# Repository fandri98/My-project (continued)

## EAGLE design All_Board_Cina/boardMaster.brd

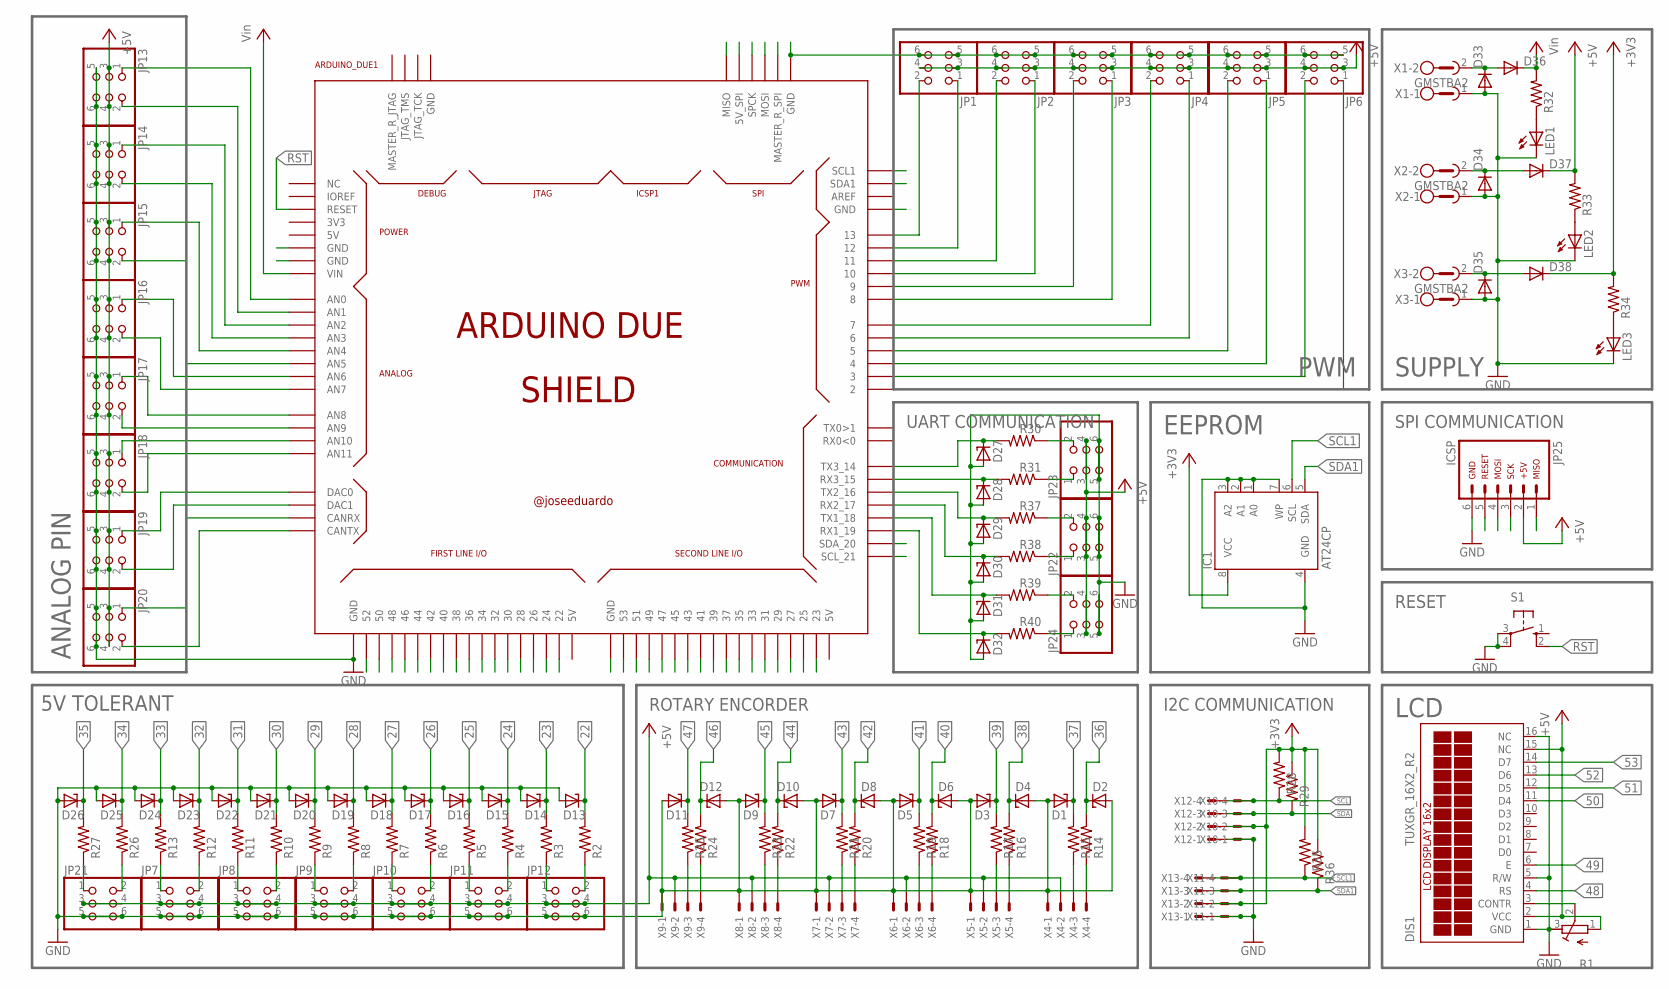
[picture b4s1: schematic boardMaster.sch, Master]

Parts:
ARDUINO_DUE1: ARDUINO_DUE_SHIELD
D1, D2, D3, D4, D5, D6, D7, D8, D9, D10, D11, D12, D13, D14, D15, D16, D17, D18, D19, D20, D21, D22, D23, D24, D25, D26, D27, D28, D29, D30, D31, D32: ZENER-DIODESOD80C; SOD80C
D33, D34, D35, D36, D37, D38: DIODE-DO214AA; DO214AA
DIS1: TUXGR_16X2_R2
IC1: AT24CP; DIL08
JP1, JP2, JP3, JP4, JP5, JP6, JP7, JP8, JP9, JP10, JP11, JP12, JP13, JP14, JP15, JP16, JP17, JP18, JP19, JP20, JP21, JP22, JP23, JP24: PINHD-2X3; 2X03
JP25: ARDUINO_CONN-ICSP; CONN-2X03
LED1, LED2, LED3: LEDCHIPLED_1206; CHIPLED_1206
R1: R-TRIMM64W; RTRIM64W
R2, R3, R4, R5, R6, R7, R8, R9, R10, R11, R12, R13, R14, R15, R16, R17, R18, R19, R20, R21, R22, R23, R24, R25, R26, R27, R28, R29, R30, R31, R32, R33, R34, R35, R36, R37, R38, R39, R40: R-US_R0805; R0805
S1: 40-XX; B3F-40XX
X1, X2, X3: GMSTBA2
X4, X5, X6, X7, X8, X9, X10, X11, X12, X13: 22-23-2041

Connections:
22: ARDUINO_DUE1.22, D13.C, R2.2
23: ARDUINO_DUE1.23, D14.C, R3.2
24: ARDUINO_DUE1.24, D15.C, R4.2
25: ARDUINO_DUE1.25, D16.C, R5.2
26: ARDUINO_DUE1.26, D17.C, R6.2
27: ARDUINO_DUE1.27, D18.C, R7.2
28: ARDUINO_DUE1.28, D19.C, R8.2
29: ARDUINO_DUE1.29, D20.C, R9.2
30: ARDUINO_DUE1.30, D21.C, R10.2
31: ARDUINO_DUE1.31, D22.C, R11.2
32: ARDUINO_DUE1.32, D23.C, R12.2
33: ARDUINO_DUE1.33, D24.C, R13.2
34: ARDUINO_DUE1.34, D25.C, R26.2
35: ARDUINO_DUE1.35, D26.C, R27.2
36: ARDUINO_DUE1.36, D2.C, R14.2
37: ARDUINO_DUE1.37, D1.C, R15.2
38: ARDUINO_DUE1.38, D4.C, R16.2
39: ARDUINO_DUE1.39, D3.C, R17.2
40: ARDUINO_DUE1.40, D6.C, R18.2
41: ARDUINO_DUE1.41, D5.C, R19.2
42: ARDUINO_DUE1.42, D8.C, R20.2
43: ARDUINO_DUE1.43, D7.C, R21.2
44: ARDUINO_DUE1.44, D10.C, R22.2
45: ARDUINO_DUE1.45, D9.C, R23.2
46: ARDUINO_DUE1.46, D12.C, R24.2
47: ARDUINO_DUE1.47, D11.C, R25.2
48: ARDUINO_DUE1.48, DIS1.4 (RS)
49: ARDUINO_DUE1.49, DIS1.6 (E)
50: ARDUINO_DUE1.50, DIS1.11 (D4)
51: ARDUINO_DUE1.51, DIS1.12 (D5)
52: ARDUINO_DUE1.52, DIS1.13 (D6)
53: ARDUINO_DUE1.53, DIS1.14 (D7)
+3V3: D38.C, IC1.8 (VCC), R28.2, R29.2, R34.2, R35.2, R36.2, X10.2, X11.2, X12.2, X13.2
+5V: ARDUINO_DUE1.5V_2 (5V_SPI), D37.C, DIS1.2 (VCC), DIS1.15 (NC), JP1.3, JP1.4, JP2.3, JP2.4, JP3.3, JP3.4, JP4.3, JP4.4, JP5.3, JP5.4, JP6.3, JP6.4, JP7.3, JP7.4, JP8.3, JP8.4, JP9.3, JP9.4, JP10.3, JP10.4, JP11.3, JP11.4, JP12.3, JP12.4, JP13.3, JP13.4, JP14.3, JP14.4, JP15.3, JP15.4, JP16.3, JP16.4, JP17.3, JP17.4, JP18.3, JP18.4, JP19.3, JP19.4, JP20.3, JP20.4, JP21.3, JP21.4, JP22.3, JP22.4, JP23.3, JP23.4, JP24.3, JP24.4, JP25.2, R1.1 (A), R33.2, X4.2, X5.2, X6.2, X7.2, X8.2, X9.2
GND: ARDUINO_DUE1.GND, ARDUINO_DUE1.GND_1 (GND), ARDUINO_DUE1.GND_2 (GND), ARDUINO_DUE1.GND_3 (GND), ARDUINO_DUE1.GND_4 (GND), ARDUINO_DUE1.GND_5 (GND), D1.A, D2.A, D3.A, D4.A, D5.A, D6.A, D7.A, D8.A, D9.A, D10.A, D11.A, D12.A, D13.A, D14.A, D15.A, D16.A, D17.A, D18.A, D19.A, D20.A, D21.A, D22.A, D23.A, D24.A, D25.A, D26.A, D27.A, D28.A, D29.A, D30.A, D31.A, D32.A, D33.A, D34.A, D35.A, DIS1.1 (GND), DIS1.5 (R/W), DIS1.16 (NC), IC1.1 (A0), IC1.2 (A1), IC1.3 (A2), IC1.4 (GND), IC1.7 (WP), JP1.5, JP1.6, JP2.5, JP2.6, JP3.5, JP3.6, JP4.5, JP4.6, JP5.5, JP5.6, JP6.5, JP6.6, JP7.5, JP7.6, JP8.5, JP8.6, JP9.5, JP9.6, JP10.5, JP10.6, JP11.5, JP11.6, JP12.5, JP12.6, JP13.5, JP13.6, JP14.5, JP14.6, JP15.5, JP15.6, JP16.5, JP16.6, JP17.5, JP17.6, JP18.5, JP18.6, JP19.5, JP19.6, JP20.5, JP20.6, JP21.5, JP21.6, JP22.5, JP22.6, JP23.5, JP23.6, JP24.5, JP24.6, JP25.6, LED1.C, LED2.C, LED3.C, R1.3 (E), S1.3, S1.4 (P1), X1.1, X2.1, X3.1, X4.1, X5.1, X6.1, X7.1, X8.1, X9.1, X10.1, X11.1, X12.1, X13.1
MISO: ARDUINO_DUE1.MISO, JP25.1
MOSI: ARDUINO_DUE1.MOSI, JP25.4
unnamed: ARDUINO_DUE1.A9 (AN9), JP17.2
unnamed: LED2.A, R33.1
unnamed: LED3.A, R34.1
unnamed: LED1.A, R32.1
unnamed: ARDUINO_DUE1.A0 (AN0), JP13.1
unnamed: ARDUINO_DUE1.A1 (AN1), JP13.2
unnamed: ARDUINO_DUE1.A2 (AN2), JP14.1
unnamed: ARDUINO_DUE1.A3 (AN3), JP14.2
unnamed: JP21.1, R27.1
unnamed: JP21.2, R26.1
unnamed: JP7.1, R13.1
unnamed: JP7.2, R12.1
unnamed: JP8.1, R11.1
unnamed: JP8.2, R10.1
unnamed: JP9.1, R9.1
unnamed: JP9.2, R8.1
unnamed: JP10.1, R7.1
unnamed: JP10.2, R6.1
unnamed: JP11.1, R5.1
unnamed: JP11.2, R4.1
unnamed: ARDUINO_DUE1.3, JP6.2
unnamed: ARDUINO_DUE1.4, JP5.1
unnamed: ARDUINO_DUE1.5, JP5.2
unnamed: ARDUINO_DUE1.6, JP4.1
unnamed: ARDUINO_DUE1.7, JP4.2
unnamed: ARDUINO_DUE1.8, JP3.1
unnamed: ARDUINO_DUE1.9, JP3.2
unnamed: ARDUINO_DUE1.10, JP2.1
unnamed: ARDUINO_DUE1.11, JP2.2
unnamed: ARDUINO_DUE1.12, JP1.1
unnamed: ARDUINO_DUE1.13, JP1.2
unnamed: ARDUINO_DUE1.A4 (AN4), JP15.1
unnamed: ARDUINO_DUE1.A5 (AN5), JP15.2
unnamed: ARDUINO_DUE1.A6 (AN6), JP16.1
unnamed: ARDUINO_DUE1.A7 (AN7), JP16.2
unnamed: ARDUINO_DUE1.A8 (AN8), JP17.1
unnamed: D33.C, D36.A, X1.2
unnamed: ARDUINO_DUE1.A10 (AN10), JP18.1
unnamed: ARDUINO_DUE1.A11 (AN11), JP18.2
unnamed: ARDUINO_DUE1.DAC0, JP19.1
unnamed: ARDUINO_DUE1.DAC1, JP19.2
unnamed: ARDUINO_DUE1.CANRX, JP20.1
unnamed: ARDUINO_DUE1.CANTX, JP20.2
unnamed: JP23.2, R30.1
unnamed: JP23.1, R31.1
unnamed: D34.C, D37.A, X2.2
unnamed: D35.C, D38.A, X3.2
unnamed: JP22.2, R37.1
unnamed: JP22.1, R38.1
unnamed: JP24.1, R40.1
unnamed: R14.1, X4.4
unnamed: JP24.2, R39.1
unnamed: JP12.1, R3.1
unnamed: JP12.2, R2.1
unnamed: R15.1, X4.3
unnamed: R16.1, X5.4
unnamed: R17.1, X5.3
unnamed: R18.1, X6.4
unnamed: R19.1, X6.3
unnamed: R20.1, X7.4
unnamed: R21.1, X7.3
unnamed: R22.1, X8.4
unnamed: R23.1, X8.3
unnamed: R24.1, X9.4
unnamed: R25.1, X9.3
unnamed: DIS1.3 (CONTR), R1.2 (S)
unnamed: ARDUINO_DUE1.14 (TX3_14), D27.C, R30.2
unnamed: ARDUINO_DUE1.15 (RX3_15), D28.C, R31.2
unnamed: ARDUINO_DUE1.16 (TX2_16), D29.C, R37.2
unnamed: ARDUINO_DUE1.17 (RX2_17), D30.C, R38.2
unnamed: ARDUINO_DUE1.19 (RX1_19), D32.C, R40.2
unnamed: ARDUINO_DUE1.2, JP6.1
unnamed: ARDUINO_DUE1.18 (TX1_18), D31.C, R39.2
RST: ARDUINO_DUE1.RESET, S1.2 (S1)
SCK: ARDUINO_DUE1.SPCK, JP25.3
SCL: ARDUINO_DUE1.21 (SCL_21), R28.1, X10.4, X12.4
SCL1: ARDUINO_DUE1.SCL1, IC1.6 (SCL), R35.1, X11.4, X13.4
SDA: ARDUINO_DUE1.20 (SDA_20), R29.1, X10.3, X12.3
SDA1: ARDUINO_DUE1.SDA1, IC1.5 (SDA), R36.1, X11.3, X13.3
SS: ARDUINO_DUE1.MASTER_RESET_SPI (MASTER_R_SPI), JP25.5
VCC: ARDUINO_DUE1.VIN, D36.C, R32.2

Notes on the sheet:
ANALOG PIN
5V TOLERANT
ROTARY ENCORDER
I2C COMMUNICATION
LCD
RESET
SPI COMMUNICATION
SUPPLY
PWM
EEPROM
UART COMMUNICATION

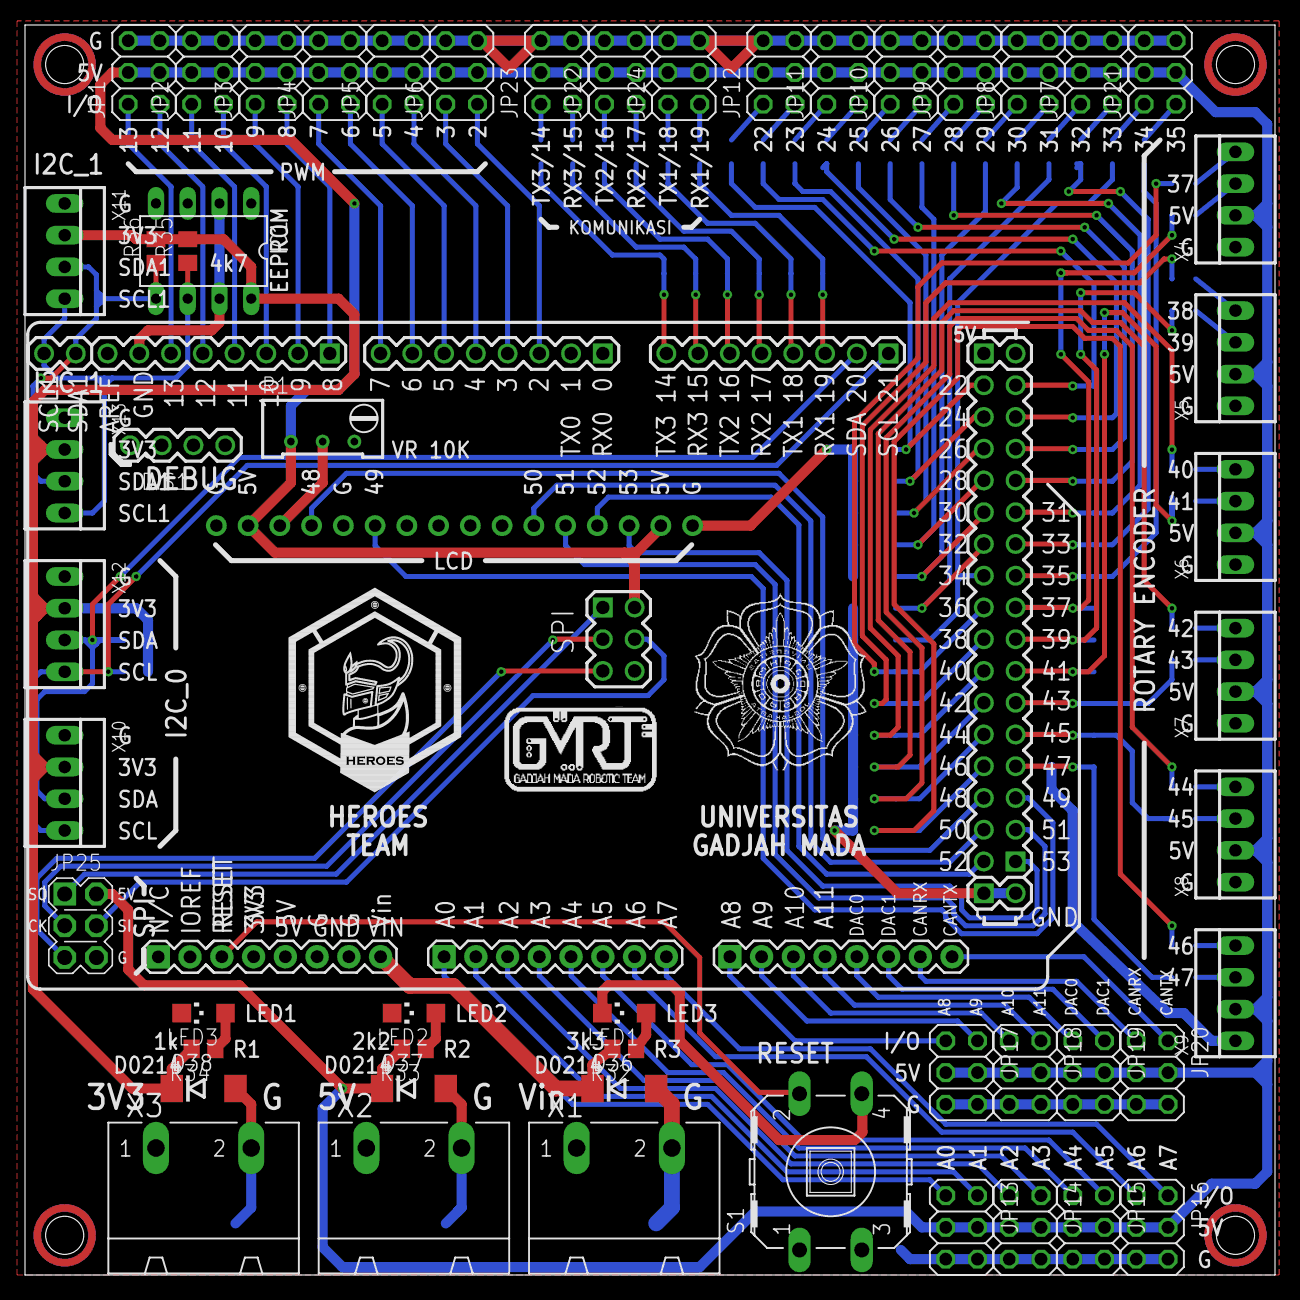
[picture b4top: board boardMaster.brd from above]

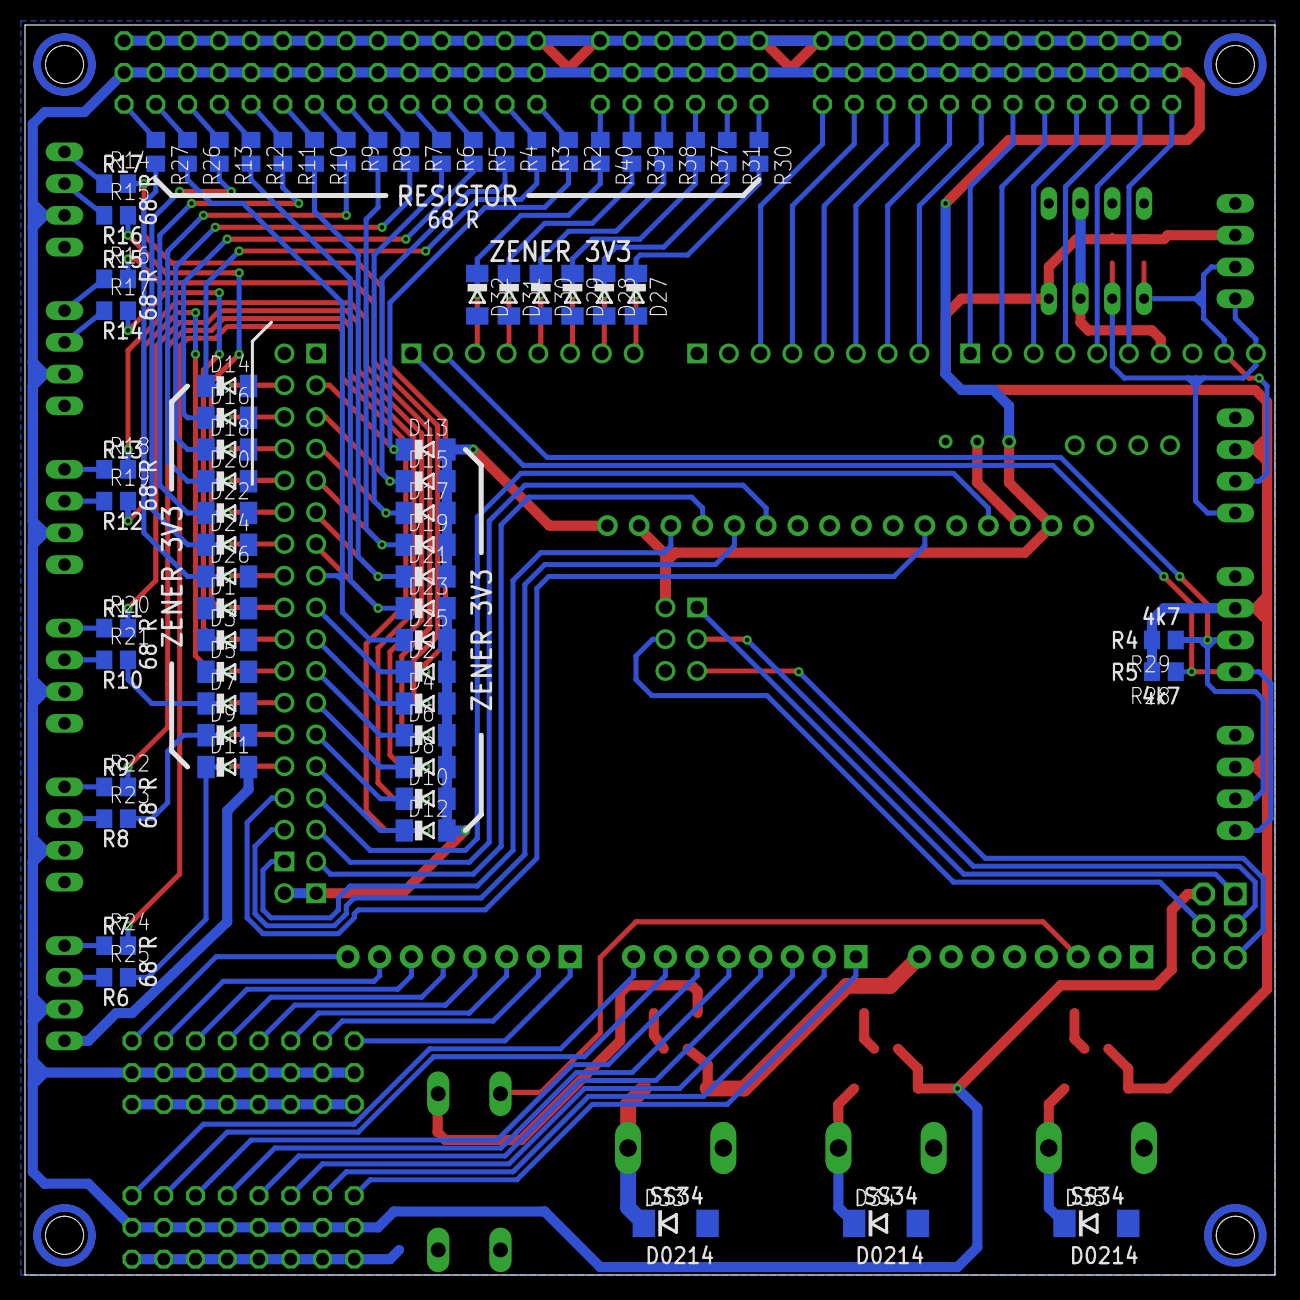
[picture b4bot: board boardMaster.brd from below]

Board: 2 copper layers, 100.0 x 100.0 mm, 127 parts (69 on the bottom side), 118 nets.

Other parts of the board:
U$1, U$2, U$3, U$4: HOLE-3MM

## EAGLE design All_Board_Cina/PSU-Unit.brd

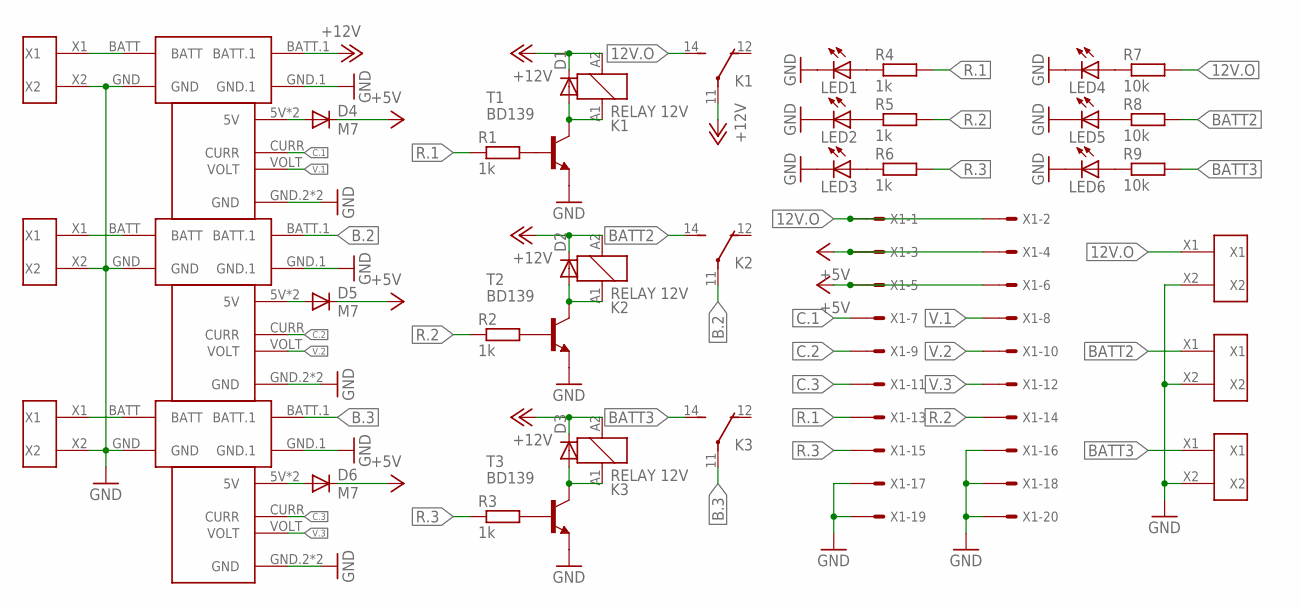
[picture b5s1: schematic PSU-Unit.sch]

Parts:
D1, D2, D3: DIODE-DO214AA; DO214AA
D4, D5, D6: M7; DO214AA
K1, K2, K3: RELAY 12V; ZD1
LED1, LED2, LED3, LED4, LED5, LED6: LEDCHIPLED_1206; CHIPLED_1206
R1, R2, R3, R4, R5, R6: 1k; R0805
R7, R8, R9: 10k; R0805
T1, T2, T3: BD139; TO126V
U$1, U$3, U$5: APM-POWER-MODULE
U$2, U$4, U$6: APM-MEASURAND
U$7, U$8, U$9, U$10, U$11, U$12: T-BLOCK-9.5MM
X1: 057-020-1

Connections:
12V.O: K1.14 (S), R7.2, U$10.X1, X1.1, X1.2
+5V: D4.C, D5.C, D6.C, X1.3, X1.4, X1.5, X1.6
+12V: D1.C, D2.C, D3.C, K1.11, K1.A2 (2), K2.A2 (2), K3.A2 (2), U$1.BATT.1
B.2: K2.11, U$3.BATT.1
B.3: K3.11, U$5.BATT.1
BATT2: K2.14 (S), R8.2, U$11.X1
BATT3: K3.14 (S), R9.2, U$12.X1
C.1: U$2.CURR, X1.7
C.2: U$4.CURR, X1.9
C.3: U$6.CURR, X1.11
GND: LED1.C, LED2.C, LED3.C, LED4.C, LED5.C, LED6.C, T1.1 (E), T2.1 (E), T3.1 (E), U$1.GND, U$1.GND.1, U$2.GND.2 (GND), U$2.GND.3 (GND), U$3.GND, U$3.GND.1, U$4.GND.2 (GND), U$4.GND.3 (GND), U$5.GND, U$5.GND.1, U$6.GND.2 (GND), U$6.GND.3 (GND), U$7.X2, U$8.X2, U$9.X2, U$10.X2, U$11.X2, U$12.X2, X1.16, X1.17, X1.18, X1.19, X1.20
unnamed: D1.A, K1.A1 (1), T1.2 (C)
unnamed: D4.A, U$2.5V, U$2.5V.1 (5V)
unnamed: R1.2, T1.3 (B)
unnamed: D5.A, U$4.5V, U$4.5V.1 (5V)
unnamed: D2.A, K2.A1 (1), T2.2 (C)
unnamed: R2.2, T2.3 (B)
unnamed: D6.A, U$6.5V, U$6.5V.1 (5V)
unnamed: D3.A, K3.A1 (1), T3.2 (C)
unnamed: R3.2, T3.3 (B)
unnamed: U$1.BATT, U$7.X1
unnamed: U$3.BATT, U$8.X1
unnamed: U$5.BATT, U$9.X1
unnamed: LED1.A, R4.1
unnamed: LED2.A, R5.1
unnamed: LED3.A, R6.1
unnamed: LED4.A, R7.1
unnamed: LED5.A, R8.1
unnamed: LED6.A, R9.1
R.1: R1.1, R4.2, X1.13
R.2: R2.1, R5.2, X1.14
R.3: R3.1, R6.2, X1.15
V.1: U$2.VOLT, X1.8
V.2: U$4.VOLT, X1.10
V.3: U$6.VOLT, X1.12

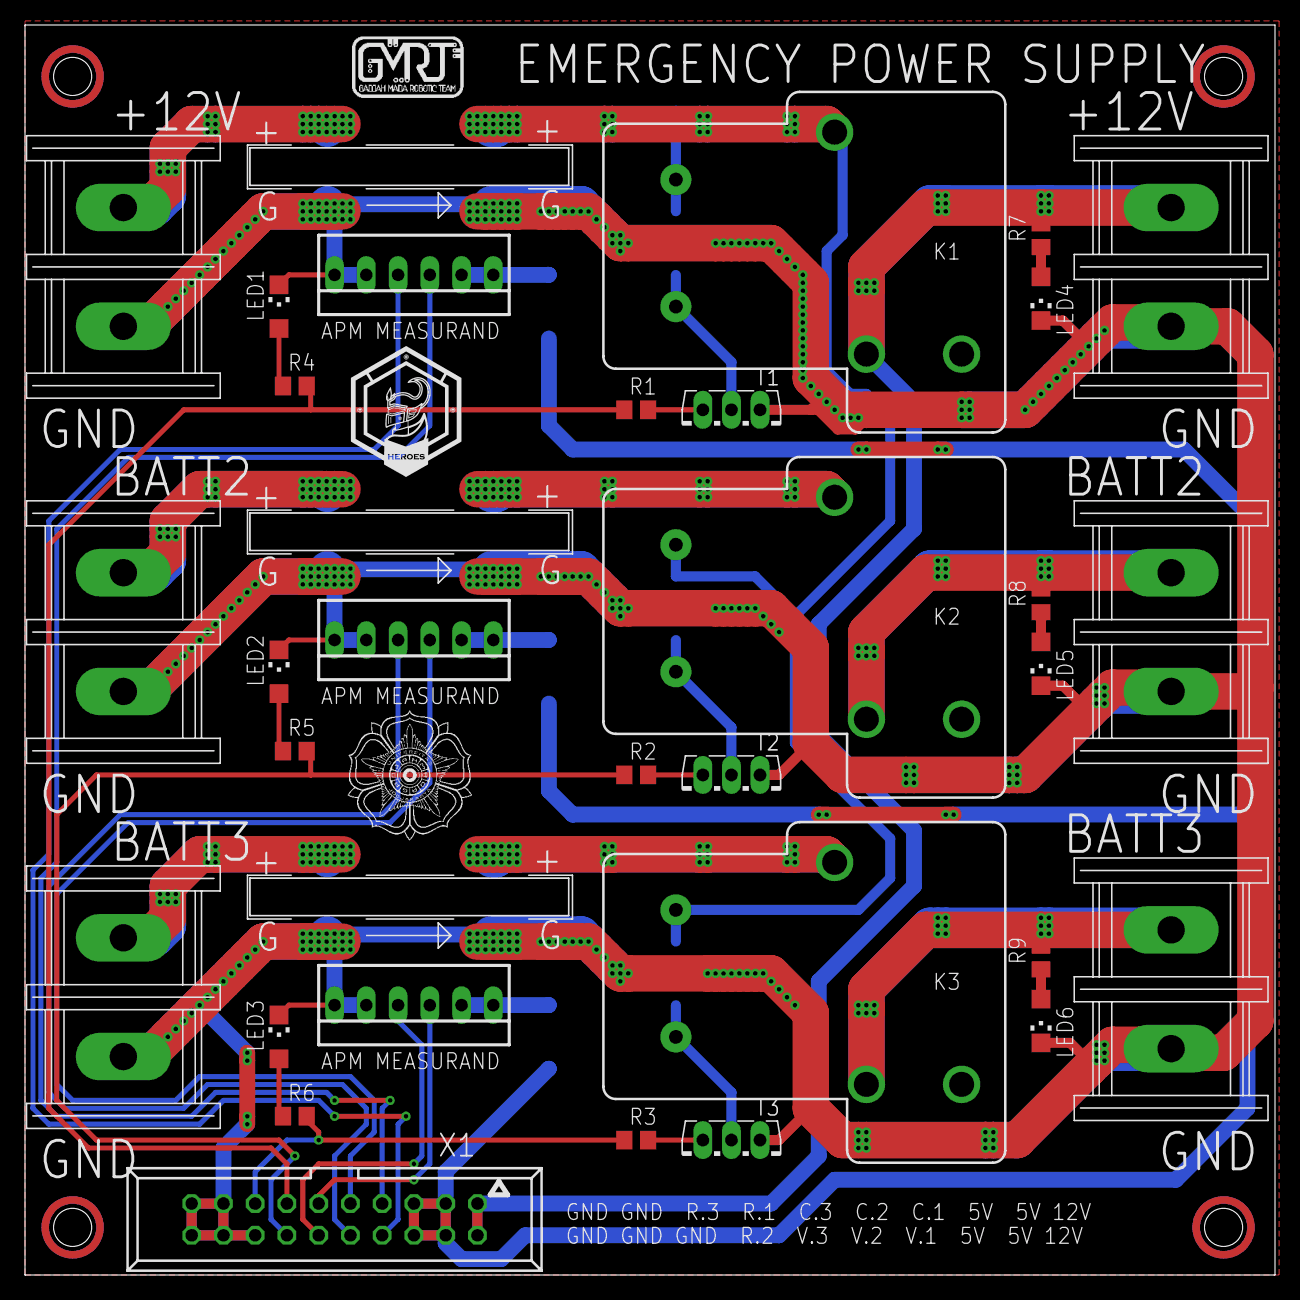
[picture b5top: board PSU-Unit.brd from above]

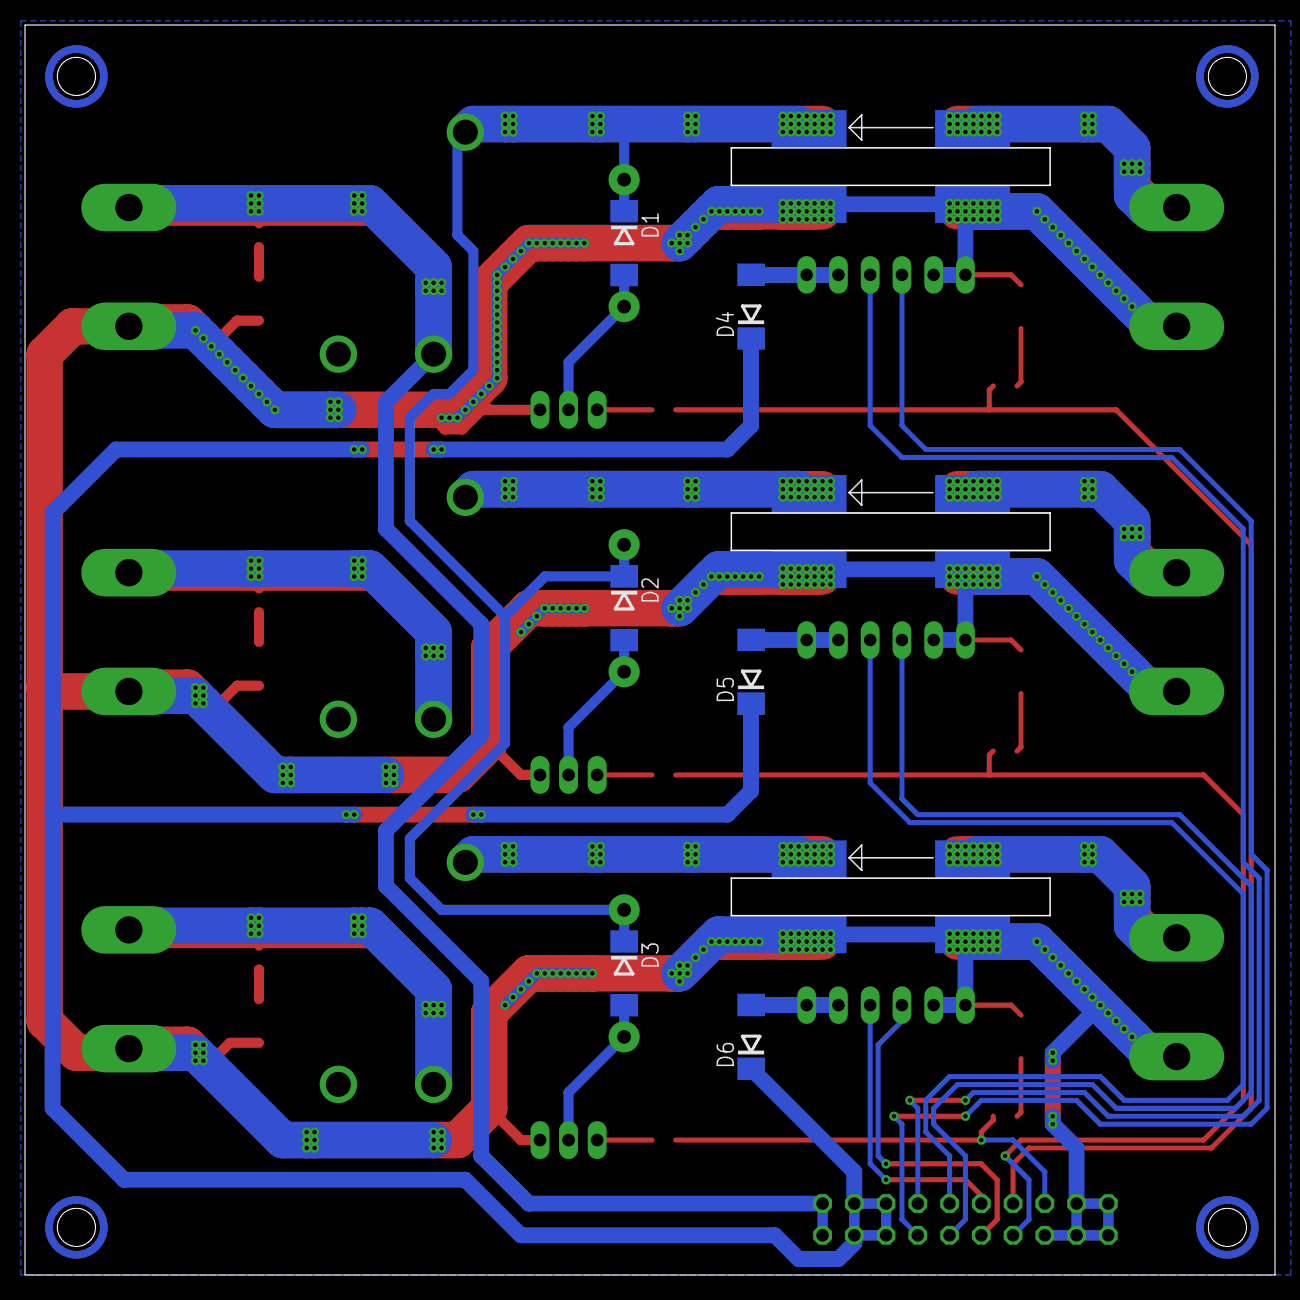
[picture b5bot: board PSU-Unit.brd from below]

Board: 2 copper layers, 100.0 x 100.0 mm, 44 parts (6 on the bottom side), 35 nets.

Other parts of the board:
U$13, U$14, U$15, U$16: HOLE-3MM

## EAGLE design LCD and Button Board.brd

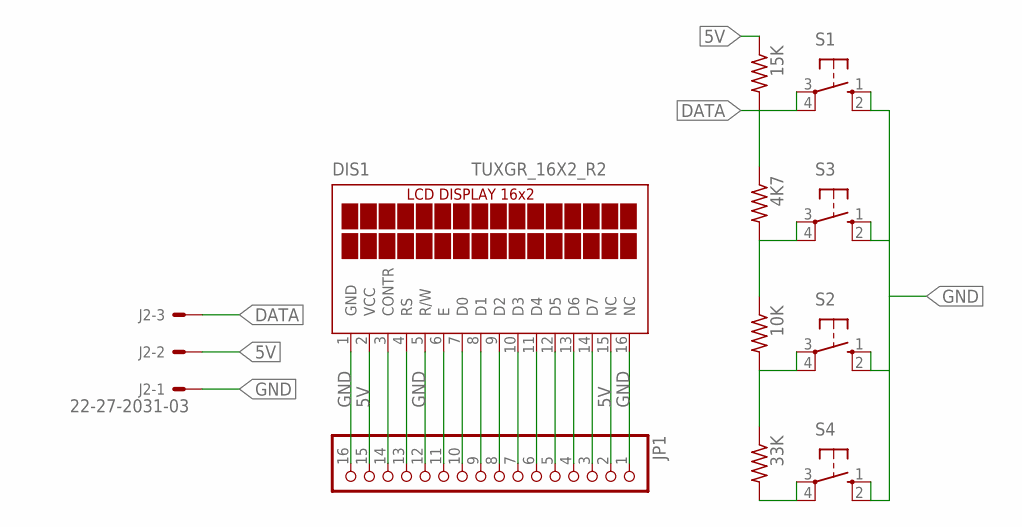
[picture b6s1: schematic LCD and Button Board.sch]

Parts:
4K7, 10K, 15K, 33K: R-US_0207/10; 0207/10
DIS1: TUXGR_16X2_R2
J2: 22-27-2031-03; 6410-03
JP1: PINHD-1X16; 1X16
S1, S2, S3, S4: 40-XX; B3F-40XX

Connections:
5V: 15K.1, DIS1.2 (VCC), DIS1.15 (NC), J2.2, JP1.2, JP1.15
DATA: 4K7.1, 15K.2, J2.3, S1.3, S1.4 (P1)
GND: DIS1.1 (GND), DIS1.5 (R/W), DIS1.16 (NC), J2.1, JP1.1, JP1.12, JP1.16, S1.1 (S), S1.2 (S1), S2.1 (S), S2.2 (S1), S3.1 (S), S3.2 (S1), S4.1 (S), S4.2 (S1)
unnamed: DIS1.3 (CONTR), JP1.14
unnamed: DIS1.4 (RS), JP1.13
unnamed: DIS1.6 (E), JP1.11
unnamed: DIS1.7 (D0), JP1.10
unnamed: DIS1.8 (D1), JP1.9
unnamed: DIS1.9 (D2), JP1.8
unnamed: DIS1.10 (D3), JP1.7
unnamed: DIS1.11 (D4), JP1.6
unnamed: DIS1.12 (D5), JP1.5
unnamed: DIS1.13 (D6), JP1.4
unnamed: DIS1.14 (D7), JP1.3
unnamed: 33K.2, S4.3, S4.4 (P1)
unnamed: 10K.2, 33K.1, S2.3, S2.4 (P1)
unnamed: 4K7.2, 10K.1, S3.3, S3.4 (P1)

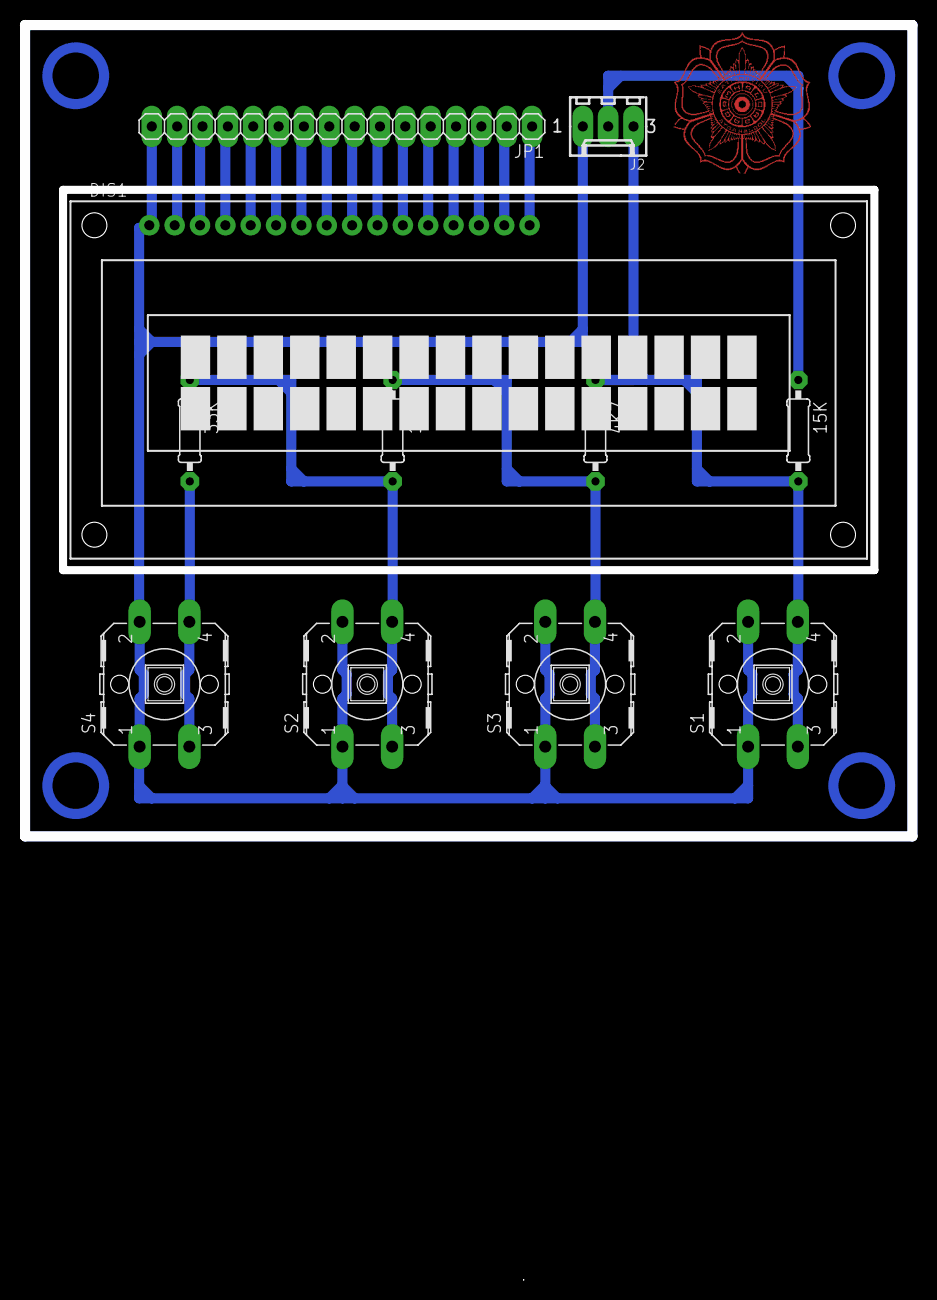
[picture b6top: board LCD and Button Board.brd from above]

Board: 2 copper layers, 88.9 x 81.3 mm, 11 parts (0 on the bottom side), 17 nets.

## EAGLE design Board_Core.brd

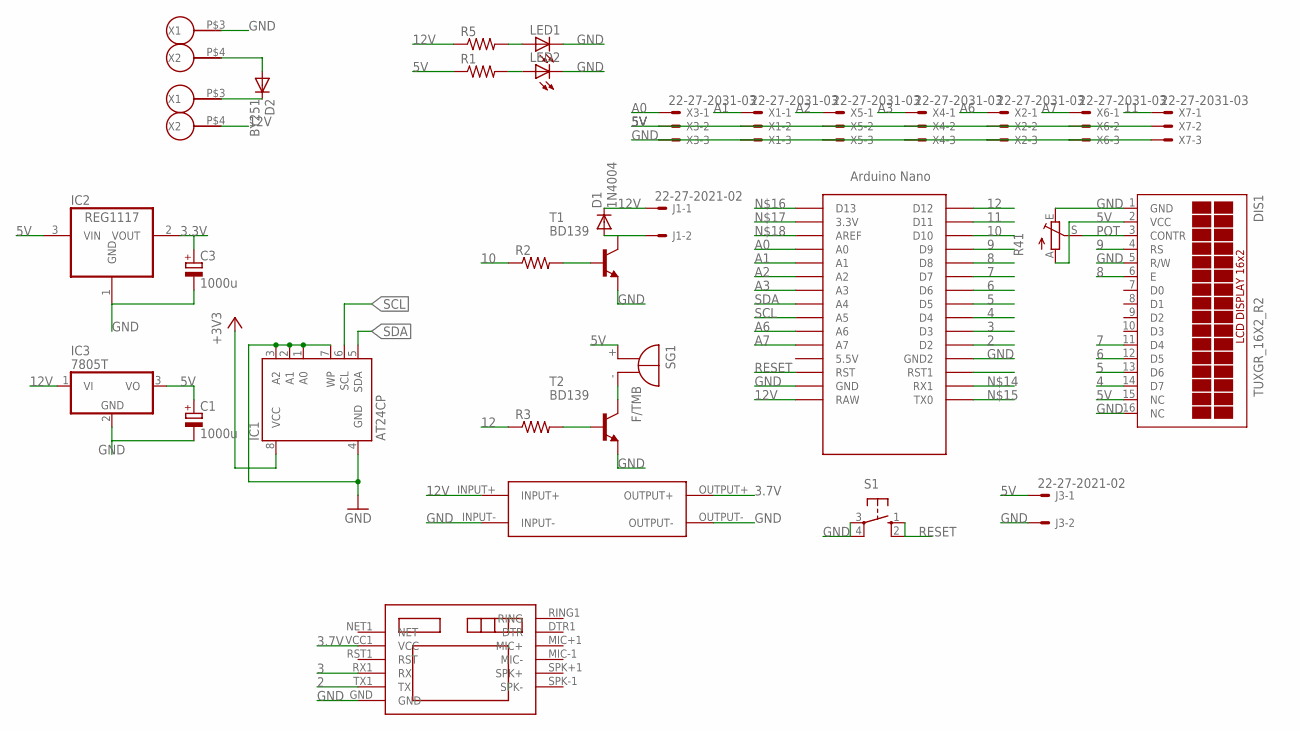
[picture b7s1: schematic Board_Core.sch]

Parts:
C1, C3: 1000u; E5-10,5
D1: 1N4004; DO41-10
D2: BY251; DO201-15
DIS1: TUXGR_16X2_R2
IC1: AT24CP; DIL08
IC2: REG1117; SOT223
IC3: 7805T; TO220H
J1, J3: 22-27-2021-02; 6410-02
LED1, LED2: LED5MM
R1, R2, R3, R5: R-US_0207/10; 0207/10
R41: TRIM_EU-CA6V; CA6V
S1: 40-XX; B3F-40XX
SG1: F/TMB
T1, T2: BD139; TO126
U$1: NANO
U$2: UBEC
U$3, U$8: TB9.5
U$4: SIM800L(F.D); SIM800L
X1, X2, X3, X4, X5, X6, X7: 22-27-2031-03; 6410-03

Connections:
2: U$1.D2, U$4.TX1 (TX)
3: U$1.D3, U$4.RX1 (RX)
3.3V: C3.+, IC1.8 (VCC), IC2.2 (VOUT)
3.7V: U$2.OUTPUT+, U$4.VCC1 (VCC)
4: DIS1.14 (D7), U$1.D4
5: DIS1.13 (D6), U$1.D5
5V: C1.+, DIS1.2 (VCC), DIS1.15 (NC), IC2.3 (VIN), IC3.3 (VO), J3.1, R1.1, R41.A, SG1.+, X1.2, X2.2, X3.2, X4.2, X5.2, X6.2, X7.2
6: DIS1.12 (D5), U$1.D6
7: DIS1.11 (D4), U$1.D7
8: DIS1.6 (E), U$1.D8
9: DIS1.4 (RS), U$1.D9
10: R2.1, U$1.D10
11: U$1.D11, X7.1
12: R3.1, U$1.D12
12V: D1.C, IC3.1 (VI), J1.1, R5.1, U$1.RAW, U$2.INPUT+, U$3.P$4 (X2)
A0: U$1.A0, X3.1
A1: U$1.A1, X1.1
A2: U$1.A2, X5.1
A3: U$1.A3, X4.1
A6: U$1.A6, X2.1
A7: U$1.A7, X6.1
GND: C1.-, C3.-, DIS1.1 (GND), DIS1.5 (R/W), DIS1.16 (NC), IC1.1 (A0), IC1.2 (A1), IC1.3 (A2), IC1.4 (GND), IC1.7 (WP), IC2.1 (GND), IC3.2 (GND), J3.2, LED1.K (C), LED2.K (C), R41.E, S1.3, S1.4 (P1), T1.1 (E), T2.1 (E), U$1.GND, U$1.GND1 (GND2), U$2.INPUT-, U$2.OUTPUT-, U$4.GND, U$8.P$3 (X1), X1.3, X2.3, X3.3, X4.3, X5.3, X6.3, X7.3
GND1: D2.A, U$8.P$4 (X2)
unnamed: LED1.A, R5.2
unnamed: R2.2, T1.3 (B)
unnamed: D1.A, J1.2, T1.2 (C)
unnamed: LED2.A, R1.2
unnamed: D2.C, U$3.P$3 (X1)
unnamed: R3.2, T2.3 (B)
unnamed: SG1.-, T2.2 (C)
POT: DIS1.3 (CONTR), R41.S
RESET: S1.1 (S), S1.2 (S1), U$1.RST
SCL: IC1.6 (SCL), U$1.A5
SDA: IC1.5 (SDA), U$1.A4

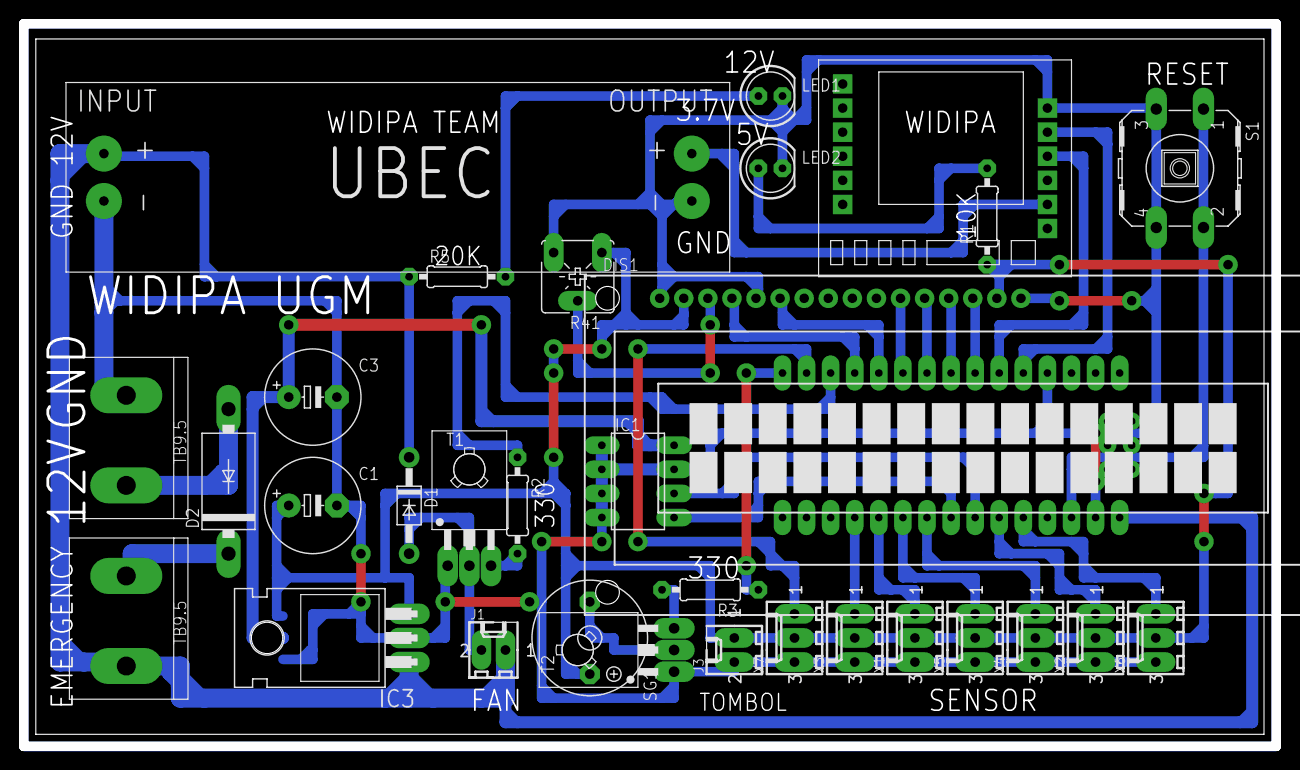
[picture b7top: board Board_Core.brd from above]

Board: 2 copper layers, 132.1 x 76.2 mm, 33 parts (1 on the bottom side), 34 nets.

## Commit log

2022-05-02 Add files via upload
    Regional 3 Robotics Board
